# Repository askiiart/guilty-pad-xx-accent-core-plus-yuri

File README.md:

# Guilty Pad XX Λ Core Plus R

This is a pretty simple TKL keyboard with backlighting, an OLED, and a rotary encoder. The fancy trick is that it's designed to work with the [GUILTY PAD -GAY-](https://github.com/askiiart/guilty-pad-gay), so you can do whatever you want with it via Bluetooth. Connect them together and use the hackpad as macro key combos or something, literally anything!

---

The woke left made me add yuri (I actually haven't added any yet, busy doing actually useful stuff)

## Bill of Materials

| Name                                                                       | Link                                                                       | Unit price | Quantity needed | MOQ | Multiple | Total per item |
| -------------------------------------------------------------------------- | -------------------------------------------------------------------------- | ---------- | --------------- | --- | -------- | -------------- |
| XIAO nrf52840                                                              | <https://www.seeedstudio.com/Seeed-XIAO-BLE-nRF52840-p-5201.html>          | 8.99       | 1               | 1   | 1        | 8.99           |
| 0402 4.7k resistors (GR0402J4K7TAG00)                                      | <https://www.lcsc.com/product-detail/C49656853.html>                       | 0          | 2               | 100 | 100      | 0.04           |
| Rotary encoder w/ switch (EC11E18244A5)                                    | <https://www.lcsc.com/product-detail/C255515.html>                         | 2.05       | 1               | 1   | 1        | 2.05           |
| 0402 806k resistor (SCR0402F806K)                                          | <https://www.lcsc.com/product-detail/C3016043.html>                        | 0          | 1               | 100 | 100      | 0.05           |
| 0402 2M resistor (GR0402J2MTAG00)                                          | <https://www.lcsc.com/product-detail/C49653113.html>                       | 0          | 1               | 100 | 100      | 0.04           |
| 0603 10uF capacitor (CL10A106MQ8NNNC)                                      | <https://www.lcsc.com/product-detail/C1691.html>                           | 0          | 1               | 50  | 50       | 0.24           |
| 60x Mill-Max hotswap sockets                                               | <https://keeb.io/products/mill-max-hotswap-sockets?variant=32377167511646> | 7.99       | 3               | 1   | 1        | 23.97          |
| 20x SK6803MINI-E (LEDs)                                                    | <https://www.aliexpress.us/item/3256807898532204.html>                     | 31.16      | 5               | 1   | 1        | 24.7           |
| 22 AWG wires w/ JST XH connectors                                          | <https://www.aliexpress.us/item/3256803495901819.html>                     | 0.99       | 1               | 1   | 1        | 0.99           |
| Complimentary P/N channel MOSFETs (G1NP02ELL)                              | <https://www.lcsc.com/product-detail/C840056.html>                         | 0.03       | 1               | 20  | 20       | 0.66           |
| 15 uH Inductor (SLW4030S150MST)                                            | <https://www.lcsc.com/product-detail/C206361.html>                         | 0.07       | 1               | 10  | 10       | 0.69           |
| 5V boost converter (H8118A40PR)                                            | <https://www.lcsc.com/product-detail/C410998.html>                         | 0.13       | 1               | 5   | 5        | 0.66           |
| Diodes (1N4001)                                                            | <https://www.lcsc.com/product-detail/C2909965.html>                        | 0          | 89              | 50  | 50       | 0.41           |
| Level shifter (74LV1T08GW-TP)                                              | <https://www.lcsc.com/product-detail/C42460230.html>                       | 0.06       | 1               | 10  | 10       | 0.57           |
| 90x MX switches (Holy Panda 55g)                                           | <https://www.aliexpress.us/item/3256805924985540.html>                     | 5.49       | 1               | 1   | 1        | 5.49           |
| IO expander (AW9523BTQR)                                                   | <https://www.lcsc.com/product-detail/C148077.html>                         | 0.35       | 1               | 1   | 1        | 0.35           |
| Keycaps                                                                    | <https://www.aliexpress.us/item/3256809006592332.html>                     | 0.99       | 1               | 1   | 1        | 0.99           |
| 5000mAh 307090 lipo                                                        | <https://www.aliexpress.us/item/3256809787664995.html>                     | $5.18      | 1               | 1   | 1        | 4.18           |
| M2 screws and heat-set inserts (10x M2x3 inserts, 6x M2x4 (5?), 4x M2xTBD) | <https://www.aliexpress.us/item/3256807644176828.html>                     | 0.99       | 1               | 1   | 0.99     | 0.99           |
| 0.91" 128x32 OLED                                                          | <https://www.aliexpress.us/item/3256804386173217.html>                     | 0.99       | 1               | 1   | 0.99     | 0.99           |
|                                                                            |                                                                            |            |                 |     |          |                |
| Component Total                                                            |                                                                            |            |                 |     |          | 78.05          |
|                                                                            |                                                                            |            |                 |     |          |                |
| PCB total                                                                  |                                                                            |            |                 |     |          | 29.74          |
| Seeed studio shipping                                                      |                                                                            |            |                 |     |          | 5.46           |
| keeb.io shipping                                                           |                                                                            |            |                 |     |          | 6.37           |
| SK6803MINI-E shipping                                                      |                                                                            |            |                 |     |          | 6.52           |
| 5000mAh lipo shipping                                                      |                                                                            |            |                 |     |          | 5.41           |
| LCSC shipping & handling                                                   |                                                                            |            |                 |     |          | 11.71          |
|                                                                            |                                                                            |            |                 |     |          |                |
| Subtotal                                                                   |                                                                            |            |                 |     |          | 143.25         |
| Without mill-max sockets                                                   |                                                                            |            |                 |     |          | 112.91         |
|                                                                            |                                                                            |            |                 |     |          |                |
| Total                                                                      |                                                                            |            |                 |     |          | 155.07         |
| **Without mill-max sockets**                                               |                                                                            |            |                 |     |          | 122.23         |

## TODO

- redo routing everything
- [crystal](https://www.lcsc.com/product-detail/C18213028.html)
  - [capacitors](https://www.lcsc.com/product-detail/C501818.html)
- [antenna](https://www.lcsc.com/product-detail/C42395593.html)
- [usb resistors](https://www.lcsc.com/product-detail/C2906874.html)
- battery management chip: [SGM40567](https://www.lcsc.com/product-detail/C5141336.html)
  - [digipot for PROG](https://www.lcsc.com/product-detail/C649485.html)
- [usb-c port](https://jlcpcb.com/partdetail/Korean_HropartsElec-TYPE_C_31_M12/C165948)
- reset button
  - [reset button?](https://www.aliexpress.us/item/3256806601702089.html)
  - [reset buttonnnnnn?](https://www.lcsc.com/product-detail/C49234121.html)
- [pmos for voltage regulators](https://www.lcsc.com/product-detail/C239037.html)
- [D4 (3A)](https://www.lcsc.com/product-detail/C97127.html)
- [D1, D2, D3, D7 (1A)](https://www.lcsc.com/product-detail/C2912031.html)
- [D5, D6 (2A)](https://www.lcsc.com/product-detail/C153761.html)
- [5V boost converter](https://www.lcsc.com/product-detail/C621881.html)

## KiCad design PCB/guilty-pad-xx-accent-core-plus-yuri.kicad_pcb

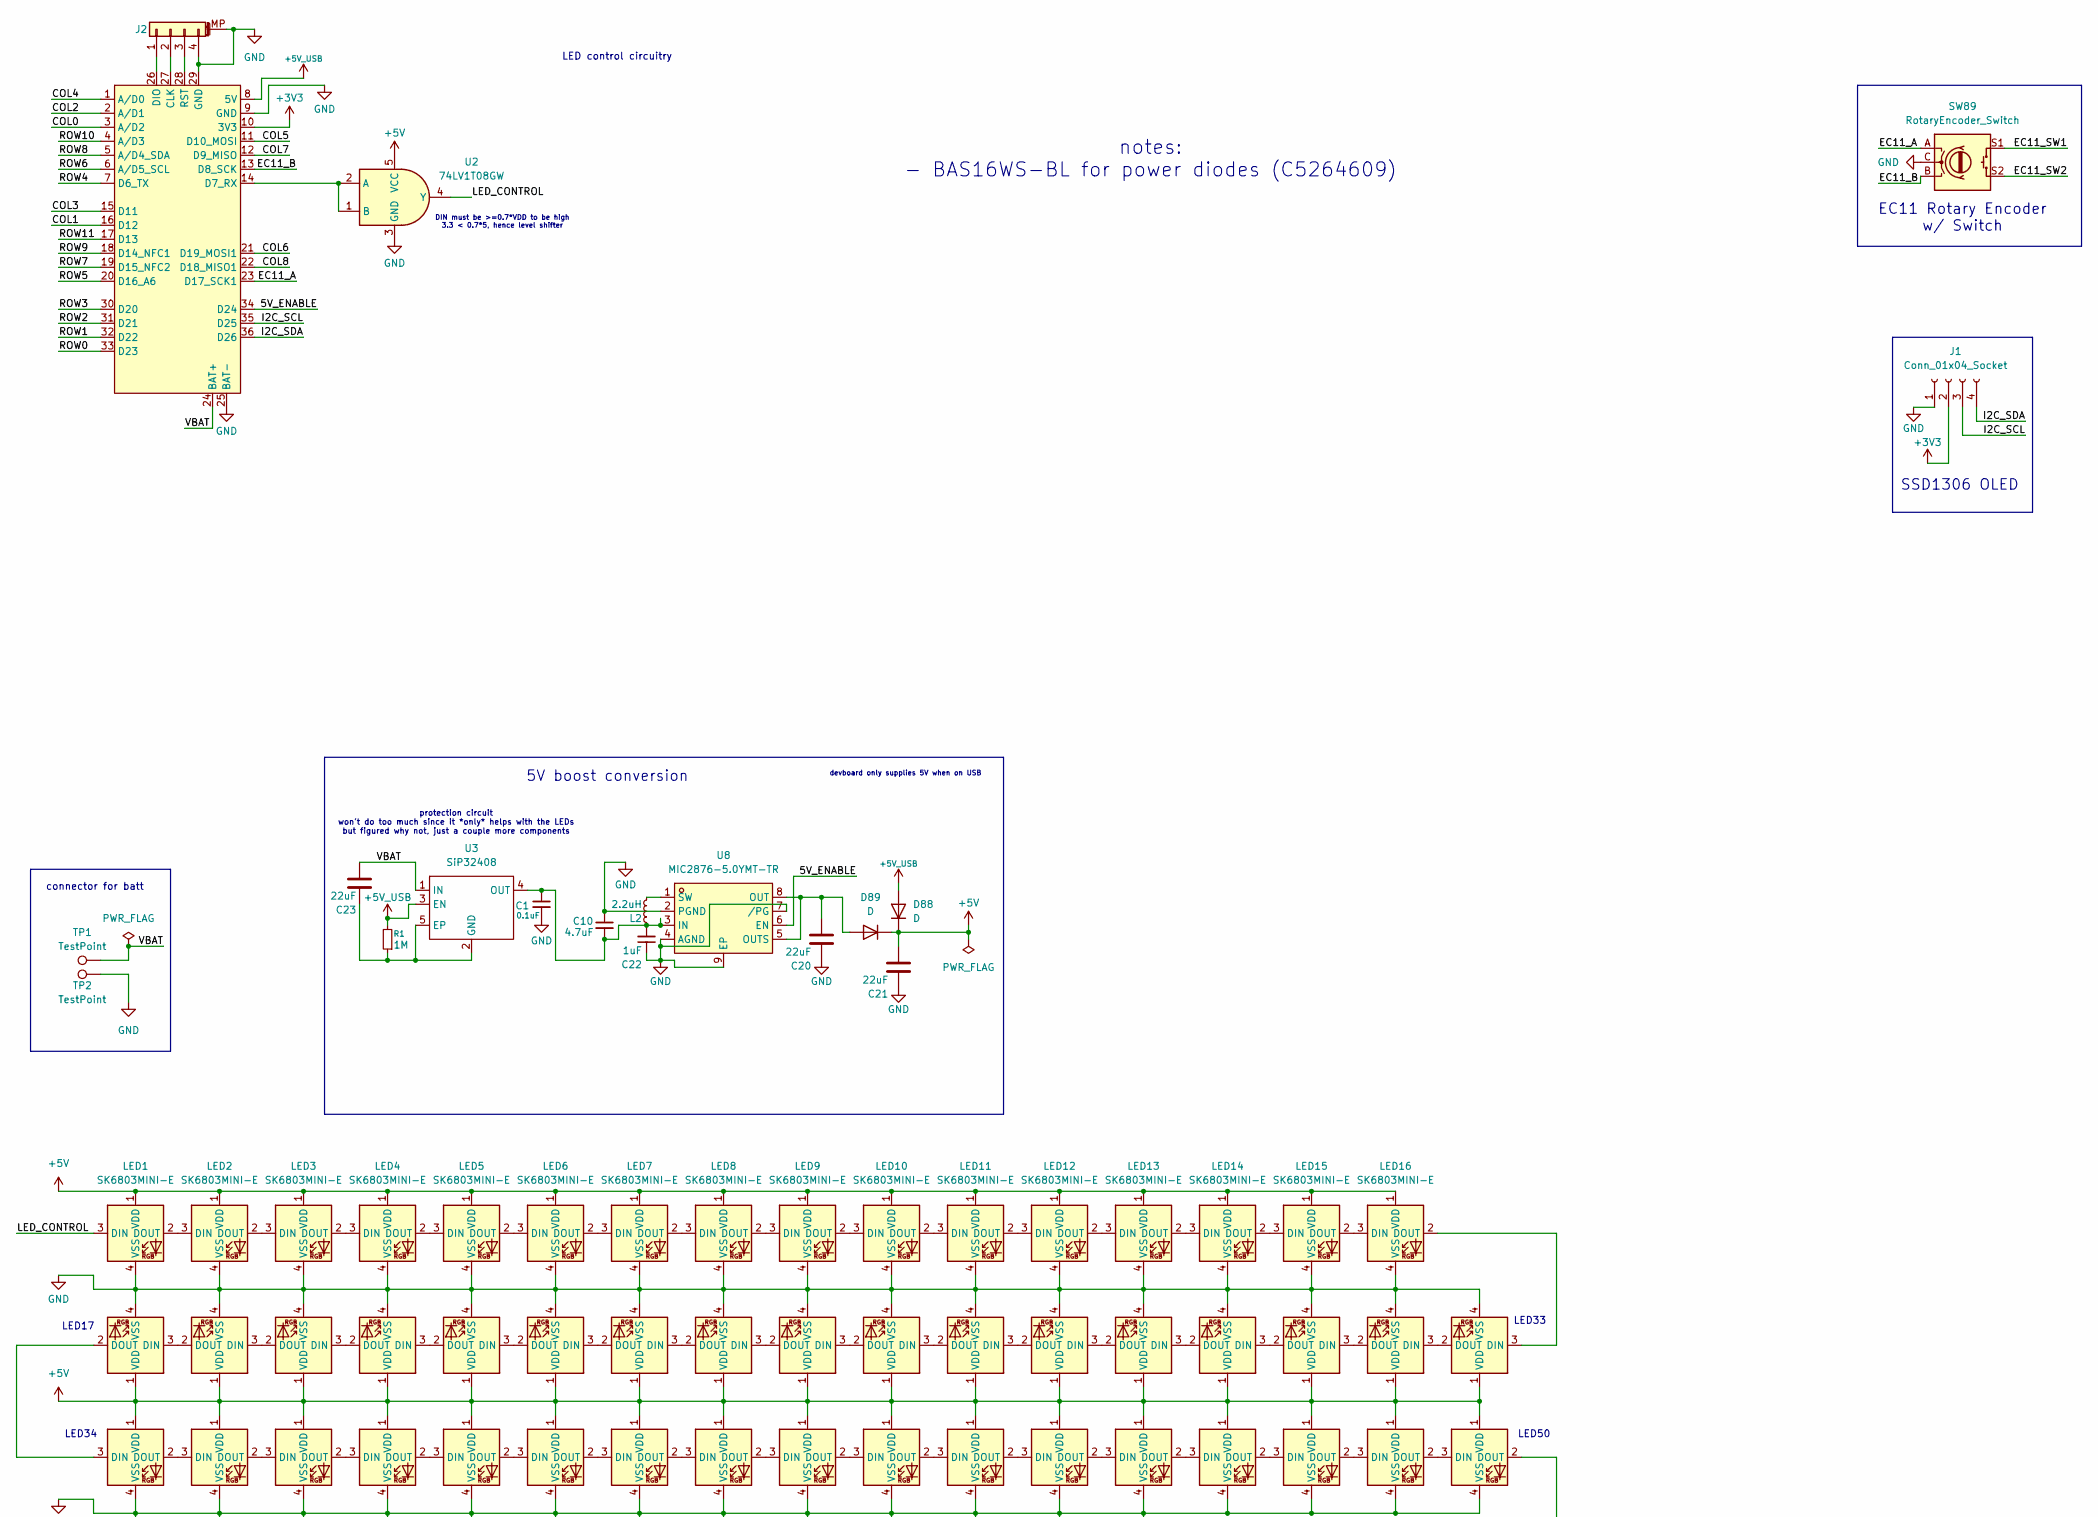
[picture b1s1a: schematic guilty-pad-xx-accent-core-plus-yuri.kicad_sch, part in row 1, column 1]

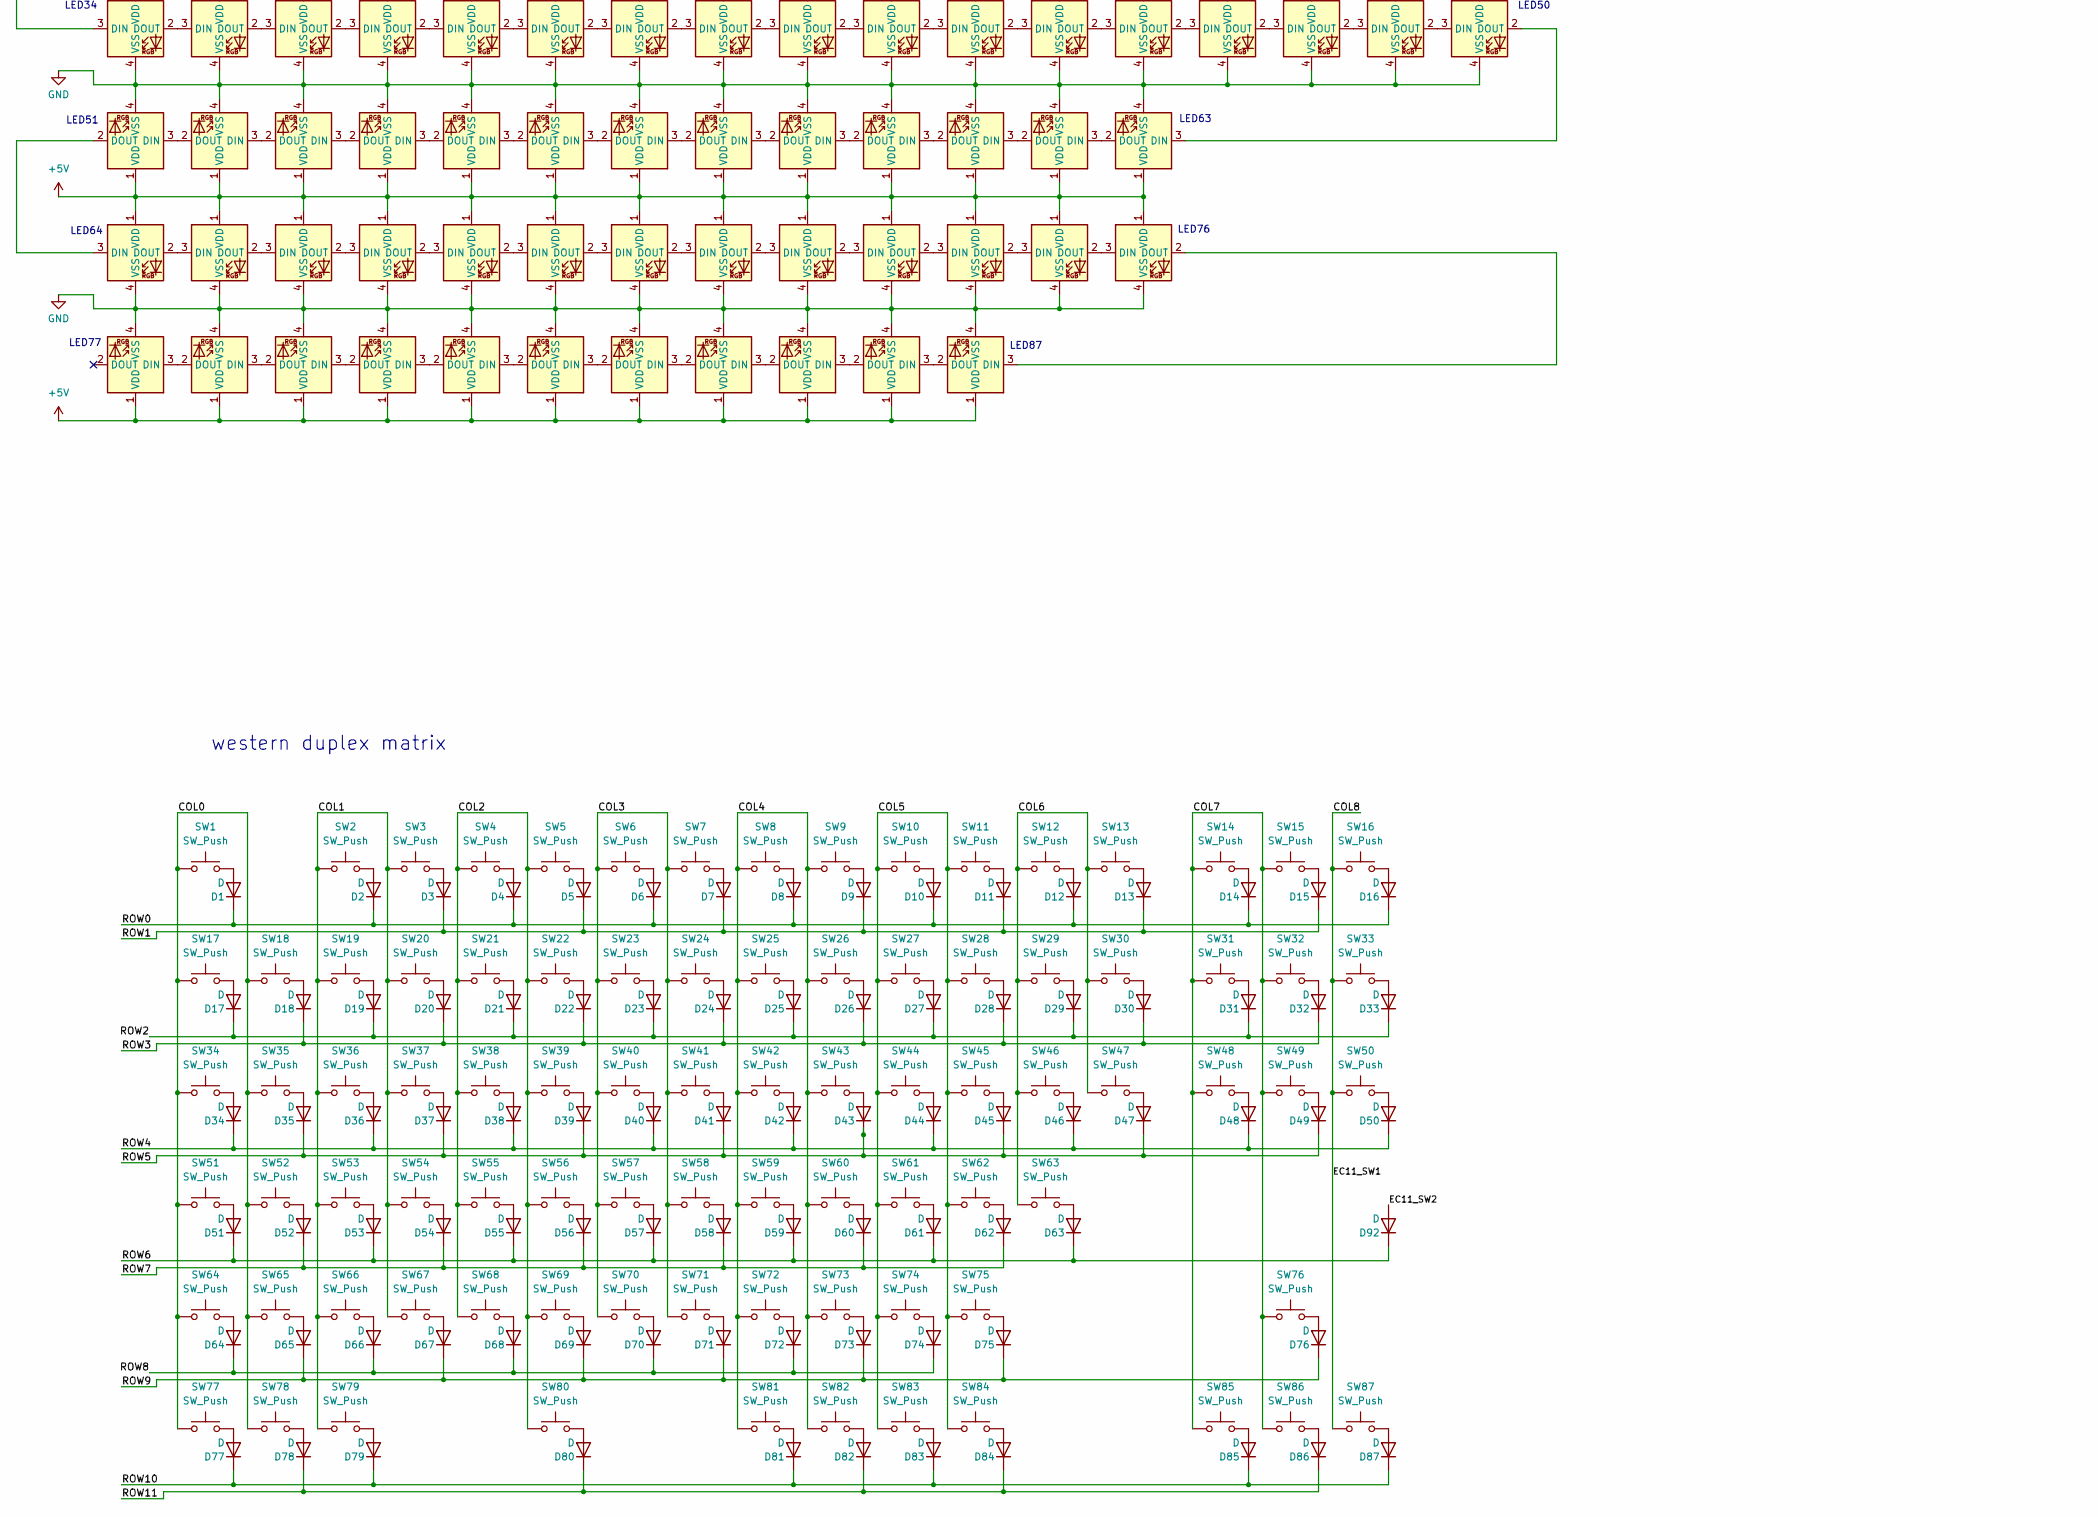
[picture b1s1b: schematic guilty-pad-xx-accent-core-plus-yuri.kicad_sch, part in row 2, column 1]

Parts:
C1: 0.1uF; C_0603_1608Metric
C10: 4.7uF; C_0603_1608Metric
C20, C21, C23: 22uF; C_0603_1608Metric
C22: 1uF; C_0603_1608Metric
D1, D2, D3, D4, D5, D6, D7, D8, D9, D10, D11, D12, D13, D14, D15, D16, D17, D18, D19, D20, D21, D22, D23, D24, D25, D26, D27, D28, D29, D30, D31, D32, D33, D34, D35, D36, D37, D38, D39, D40, D41, D42, D43, D44, D45, D46, D47, D48, D49, D50, D51, D52, D53, D54, D55, D56, D57, D58, D59, D60, D61, D62, D63, D64, D65, D66, D67, D68, D69, D70, D71, D72, D73, D74, D75, D76, D77, D78, D79, D80, D81, D82, D83, D84, D85, D86, D87, D88, D89, D92: D; D_SOD-323_HandSoldering
J1: Conn_01x04_Socket; SSD1306-0.91-OLED-4pin-128x32
J2: Conn_01x04_MountingPin; JST_SH_BM04B-SRSS-TB_1x04-1MP_P1.00mm_Vertical
L2: 2.2uH; L_0805_2012Metric
LED1, LED2, LED3, LED4, LED5, LED6, LED7, LED8, LED9, LED10, LED11, LED12, LED13, LED14, LED15, LED16, LED17, LED18, LED19, LED20, LED21, LED22, LED23, LED24, LED25, LED26, LED27, LED28, LED29, LED30, LED31, LED32, LED33, LED34, LED35, LED36, LED37, LED38, LED39, LED40, LED41, LED42, LED43, LED44, LED45, LED46, LED47, LED48, LED49, LED50, LED51, LED52, LED53, LED54, LED55, LED56, LED57, LED58, LED59, LED60, LED61, LED62, LED63, LED64, LED65, LED66, LED67, LED68, LED69, LED70, LED71, LED72, LED73, LED74, LED75, LED76, LED77, LED78, LED79, LED80, LED81, LED82, LED83, LED84, LED85, LED86, LED87: SK6803MINI-E; LED_6028R
R1: 1M; R_0603_1608Metric
SW1, SW2, SW3, SW4, SW5, SW6, SW7, SW8, SW9, SW10, SW11, SW12, SW13, SW14, SW15, SW16, SW17, SW18, SW19, SW20, SW21, SW22, SW23, SW24, SW25, SW26, SW27, SW28, SW29, SW30, SW31, SW32, SW33, SW35, SW36, SW37, SW38, SW39, SW40, SW41, SW42, SW43, SW44, SW45, SW46, SW48, SW49, SW50, SW52, SW53, SW54, SW55, SW56, SW57, SW58, SW59, SW60, SW61, SW62, SW63, SW64, SW65, SW66, SW67, SW68, SW69, SW70, SW71, SW72, SW73, SW74, SW75, SW76, SW80, SW85, SW86, SW87: SW_Push; SW_MX_HS_CPG151101S11_1u
SW34, SW47: SW_Push; SW_MX_HS_CPG151101S11_1.5u
SW51: SW_Push; SW_MX_HS_CPG151101S11_1.75u
SW77, SW78, SW79, SW81, SW82, SW83, SW84: SW_Push; SW_MX_HS_CPG151101S11_1.25u
SW89: RotaryEncoder_Switch; RotaryEncoder_Alps_EC11E-Switch_Vertical_H20mm
TP1, TP2: TestPoint; TestPoint_Pad_2.0x2.0mm
U1: Guilty Devboard Xrd; Guilty Devboard Xrd - SMD
U2: 74LV1T08GW; SOT-353_SC-70-5
U3: SiP32408; UDFN-4-1EP_1.2x1.6mm_P0.5mm_EP0.86x0.5mm
U8: MIC2876-5.0YMT-TR; UDFN-8_L2.0-W2.0-P0.50-BL-EP; LCSC Part C621881

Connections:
+3V3: J1.2, U1.10 (3V3)
+5V: C21.2, D88.1 (K), D89.1 (K), LED1.1 (VDD), LED2.1 (VDD), LED3.1 (VDD), LED4.1 (VDD), LED5.1 (VDD), LED6.1 (VDD), LED7.1 (VDD), LED8.1 (VDD), LED9.1 (VDD), LED10.1 (VDD), LED11.1 (VDD), LED12.1 (VDD), LED13.1 (VDD), LED14.1 (VDD), LED15.1 (VDD), LED16.1 (VDD), LED17.1 (VDD), LED18.1 (VDD), LED19.1 (VDD), LED20.1 (VDD), LED21.1 (VDD), LED22.1 (VDD), LED23.1 (VDD), LED24.1 (VDD), LED25.1 (VDD), LED26.1 (VDD), LED27.1 (VDD), LED28.1 (VDD), LED29.1 (VDD), LED30.1 (VDD), LED31.1 (VDD), LED32.1 (VDD), LED33.1 (VDD), LED34.1 (VDD), LED35.1 (VDD), LED36.1 (VDD), LED37.1 (VDD), LED38.1 (VDD), LED39.1 (VDD), LED40.1 (VDD), LED41.1 (VDD), LED42.1 (VDD), LED43.1 (VDD), LED44.1 (VDD), LED45.1 (VDD), LED46.1 (VDD), LED47.1 (VDD), LED48.1 (VDD), LED49.1 (VDD), LED50.1 (VDD), LED51.1 (VDD), LED52.1 (VDD), LED53.1 (VDD), LED54.1 (VDD), LED55.1 (VDD), LED56.1 (VDD), LED57.1 (VDD), LED58.1 (VDD), LED59.1 (VDD), LED60.1 (VDD), LED61.1 (VDD), LED62.1 (VDD), LED63.1 (VDD), LED64.1 (VDD), LED65.1 (VDD), LED66.1 (VDD), LED67.1 (VDD), LED68.1 (VDD), LED69.1 (VDD), LED70.1 (VDD), LED71.1 (VDD), LED72.1 (VDD), LED73.1 (VDD), LED74.1 (VDD), LED75.1 (VDD), LED76.1 (VDD), LED77.1 (VDD), LED78.1 (VDD), LED79.1 (VDD), LED80.1 (VDD), LED81.1 (VDD), LED82.1 (VDD), LED83.1 (VDD), LED84.1 (VDD), LED85.1 (VDD), LED86.1 (VDD), LED87.1 (VDD), U2.5 (VCC)
+5V_USB: D88.2 (A), R1.2, U1.8 (5V), U3.3 (EN)
/5V_ENABLE: U1.34 (D24), U8.6 (EN)
/COL0: SW1.1, SW17.1, SW18.1, SW34.1, SW35.1, SW51.1, SW52.1, SW64.1, SW65.1, SW77.1, SW78.1, U1.3 (A/D2)
/COL1: SW2.1, SW3.1, SW19.1, SW20.1, SW36.1, SW37.1, SW53.1, SW54.1, SW66.1, SW67.1, SW79.1, U1.16 (D12)
/COL2: SW4.1, SW5.1, SW21.1, SW22.1, SW38.1, SW39.1, SW55.1, SW56.1, SW68.1, SW69.1, SW80.1, U1.2 (A/D1)
/COL3: SW6.1, SW7.1, SW23.1, SW24.1, SW40.1, SW41.1, SW57.1, SW58.1, SW70.1, SW71.1, U1.15 (D11)
/COL4: SW8.1, SW9.1, SW25.1, SW26.1, SW42.1, SW43.1, SW59.1, SW60.1, SW72.1, SW73.1, SW81.1, SW82.1, U1.1 (A/D0)
/COL5: SW10.1, SW11.1, SW27.1, SW28.1, SW44.1, SW45.1, SW61.1, SW62.1, SW74.1, SW75.1, SW83.1, SW84.1, U1.11 (D10_MOSI)
/COL6: SW12.1, SW13.1, SW29.1, SW30.1, SW46.1, SW47.1, SW63.1, U1.21 (D19_MOSI1)
/COL7: SW14.1, SW15.1, SW31.1, SW32.1, SW48.1, SW49.1, SW76.1, SW85.1, SW86.1, U1.12 (D9_MISO)
/COL8: SW16.1, SW33.1, SW50.1, SW87.1, SW89.S1, U1.22 (D18_MISO1)
/EC11_A: SW89.A, U1.23 (D17_SCK1)
/EC11_B: SW89.B, U1.13 (D8_SCK)
/EC11_SW2: D92.2 (A), SW89.S2
/I2C_SCL: J1.3, U1.35 (D25)
/I2C_SDA: J1.4, U1.36 (D26)
/LED_CONTROL: LED1.3 (DIN), U2.4 (Y)
/ROW0: D1.1 (K), D2.1 (K), D4.1 (K), D6.1 (K), D8.1 (K), D10.1 (K), D12.1 (K), D14.1 (K), D16.1 (K), U1.33 (D23)
/ROW1: D3.1 (K), D5.1 (K), D7.1 (K), D9.1 (K), D11.1 (K), D13.1 (K), D15.1 (K), U1.32 (D22)
/ROW2: D17.1 (K), D19.1 (K), D21.1 (K), D23.1 (K), D25.1 (K), D27.1 (K), D29.1 (K), D31.1 (K), D33.1 (K), U1.31 (D21)
/ROW3: D18.1 (K), D20.1 (K), D22.1 (K), D24.1 (K), D26.1 (K), D28.1 (K), D30.1 (K), D32.1 (K), U1.30 (D20)
/ROW4: D34.1 (K), D36.1 (K), D38.1 (K), D40.1 (K), D42.1 (K), D44.1 (K), D46.1 (K), D48.1 (K), D50.1 (K), U1.7 (D6_TX)
/ROW5: D35.1 (K), D37.1 (K), D39.1 (K), D41.1 (K), D43.1 (K), D45.1 (K), D47.1 (K), D49.1 (K), U1.20 (D16_A6)
/ROW6: D51.1 (K), D53.1 (K), D55.1 (K), D57.1 (K), D59.1 (K), D61.1 (K), D63.1 (K), D92.1 (K), U1.6 (A/D5_SCL)
/ROW7: D52.1 (K), D54.1 (K), D56.1 (K), D58.1 (K), D60.1 (K), D62.1 (K), U1.19 (D15_NFC2)
/ROW8: D64.1 (K), D66.1 (K), D68.1 (K), D70.1 (K), D72.1 (K), D74.1 (K), U1.5 (A/D4_SDA)
/ROW9: D65.1 (K), D67.1 (K), D69.1 (K), D71.1 (K), D73.1 (K), D75.1 (K), D76.1 (K), U1.18 (D14_NFC1)
/ROW10: D77.1 (K), D79.1 (K), D81.1 (K), D83.1 (K), D85.1 (K), D87.1 (K), U1.4 (A/D3)
/ROW11: D78.1 (K), D80.1 (K), D82.1 (K), D84.1 (K), D86.1 (K), U1.17 (D13)
/VBAT: C23.2, TP1.1 (1_1), U1.24 (BAT+), U3.1 (IN)
unnamed: D1.2 (A), SW1.2
unnamed: D2.2 (A), SW2.2
unnamed: D3.2 (A), SW3.2
unnamed: D4.2 (A), SW4.2
unnamed: D5.2 (A), SW5.2
unnamed: D6.2 (A), SW6.2
unnamed: D7.2 (A), SW7.2
unnamed: D8.2 (A), SW8.2
unnamed: D9.2 (A), SW9.2
unnamed: D10.2 (A), SW10.2
unnamed: D11.2 (A), SW11.2
unnamed: D12.2 (A), SW12.2
unnamed: D13.2 (A), SW13.2
unnamed: D14.2 (A), SW14.2
unnamed: D15.2 (A), SW15.2
unnamed: D16.2 (A), SW16.2
unnamed: D17.2 (A), SW17.2
unnamed: D18.2 (A), SW18.2
unnamed: D19.2 (A), SW19.2
unnamed: D20.2 (A), SW20.2
unnamed: D21.2 (A), SW21.2
unnamed: D22.2 (A), SW22.2
unnamed: D23.2 (A), SW23.2
unnamed: D24.2 (A), SW24.2
unnamed: D25.2 (A), SW25.2
unnamed: D26.2 (A), SW26.2
unnamed: D27.2 (A), SW27.2
unnamed: D28.2 (A), SW28.2
unnamed: D29.2 (A), SW29.2
unnamed: D30.2 (A), SW30.2
unnamed: D31.2 (A), SW31.2
unnamed: D32.2 (A), SW32.2
unnamed: D33.2 (A), SW33.2
unnamed: D34.2 (A), SW34.2
unnamed: D35.2 (A), SW35.2
unnamed: D36.2 (A), SW36.2
unnamed: D37.2 (A), SW37.2
unnamed: D38.2 (A), SW38.2
unnamed: D39.2 (A), SW39.2
unnamed: D40.2 (A), SW40.2
unnamed: D41.2 (A), SW41.2
unnamed: D42.2 (A), SW42.2
unnamed: D43.2 (A), SW43.2
unnamed: D44.2 (A), SW44.2
unnamed: D45.2 (A), SW45.2
unnamed: D46.2 (A), SW46.2
unnamed: D47.2 (A), SW47.2
unnamed: D48.2 (A), SW48.2
unnamed: D49.2 (A), SW49.2
unnamed: D50.2 (A), SW50.2
unnamed: D51.2 (A), SW51.2
unnamed: D52.2 (A), SW52.2
unnamed: D53.2 (A), SW53.2
unnamed: D54.2 (A), SW54.2
unnamed: D55.2 (A), SW55.2
unnamed: D56.2 (A), SW56.2
unnamed: D57.2 (A), SW57.2
unnamed: D58.2 (A), SW58.2
unnamed: D59.2 (A), SW59.2
unnamed: D60.2 (A), SW60.2
unnamed: D61.2 (A), SW61.2
unnamed: D62.2 (A), SW62.2
unnamed: D63.2 (A), SW63.2
unnamed: D64.2 (A), SW64.2
unnamed: D65.2 (A), SW65.2
unnamed: D66.2 (A), SW66.2
unnamed: D67.2 (A), SW67.2
unnamed: D68.2 (A), SW68.2
unnamed: D69.2 (A), SW69.2
unnamed: D70.2 (A), SW70.2
unnamed: D71.2 (A), SW71.2
unnamed: D72.2 (A), SW72.2
unnamed: D73.2 (A), SW73.2
unnamed: D74.2 (A), SW74.2
unnamed: D75.2 (A), SW75.2
unnamed: D76.2 (A), SW76.2
unnamed: D77.2 (A), SW77.2
unnamed: D78.2 (A), SW78.2
unnamed: D79.2 (A), SW79.2
unnamed: D80.2 (A), SW80.2
unnamed: D81.2 (A), SW81.2
unnamed: D82.2 (A), SW82.2
unnamed: D83.2 (A), SW83.2
unnamed: D84.2 (A), SW84.2
unnamed: D85.2 (A), SW85.2
unnamed: D86.2 (A), SW86.2
unnamed: D87.2 (A), SW87.2
unnamed: C20.2, D89.2 (A), U8.5 (OUTS), U8.8 (OUT)
unnamed: J2.1, U1.26 (DIO)
unnamed: J2.2, U1.27 (CLK)
unnamed: J2.3, U1.28 (RST)
unnamed: LED1.2 (DOUT), LED2.3 (DIN)
unnamed: LED2.2 (DOUT), LED3.3 (DIN)
unnamed: LED3.2 (DOUT), LED4.3 (DIN)
unnamed: LED4.2 (DOUT), LED5.3 (DIN)
unnamed: LED5.2 (DOUT), LED6.3 (DIN)
unnamed: LED6.2 (DOUT), LED7.3 (DIN)
unnamed: LED7.2 (DOUT), LED8.3 (DIN)
unnamed: LED8.2 (DOUT), LED9.3 (DIN)
unnamed: LED9.2 (DOUT), LED10.3 (DIN)
unnamed: LED10.2 (DOUT), LED11.3 (DIN)
unnamed: LED11.2 (DOUT), LED12.3 (DIN)
unnamed: LED12.2 (DOUT), LED13.3 (DIN)
unnamed: LED13.2 (DOUT), LED14.3 (DIN)
unnamed: LED14.2 (DOUT), LED15.3 (DIN)
unnamed: LED15.2 (DOUT), LED16.3 (DIN)
unnamed: LED16.2 (DOUT), LED33.3 (DIN)
unnamed: LED17.3 (DIN), LED18.2 (DOUT)
unnamed: LED17.2 (DOUT), LED34.3 (DIN)
unnamed: LED18.3 (DIN), LED19.2 (DOUT)
unnamed: LED19.3 (DIN), LED20.2 (DOUT)
unnamed: LED20.3 (DIN), LED21.2 (DOUT)
unnamed: LED21.3 (DIN), LED22.2 (DOUT)
unnamed: LED22.3 (DIN), LED23.2 (DOUT)
unnamed: LED23.3 (DIN), LED24.2 (DOUT)
unnamed: LED24.3 (DIN), LED25.2 (DOUT)
unnamed: LED25.3 (DIN), LED26.2 (DOUT)
unnamed: LED26.3 (DIN), LED27.2 (DOUT)
unnamed: LED27.3 (DIN), LED28.2 (DOUT)
unnamed: LED28.3 (DIN), LED29.2 (DOUT)
unnamed: LED29.3 (DIN), LED30.2 (DOUT)
unnamed: LED30.3 (DIN), LED31.2 (DOUT)
unnamed: LED31.3 (DIN), LED32.2 (DOUT)
unnamed: LED32.3 (DIN), LED33.2 (DOUT)
unnamed: LED34.2 (DOUT), LED35.3 (DIN)
unnamed: LED35.2 (DOUT), LED36.3 (DIN)
unnamed: LED36.2 (DOUT), LED37.3 (DIN)
unnamed: LED37.2 (DOUT), LED38.3 (DIN)
unnamed: LED38.2 (DOUT), LED39.3 (DIN)
unnamed: LED39.2 (DOUT), LED40.3 (DIN)
unnamed: LED40.2 (DOUT), LED41.3 (DIN)
unnamed: LED41.2 (DOUT), LED42.3 (DIN)
unnamed: LED42.2 (DOUT), LED43.3 (DIN)
unnamed: LED43.2 (DOUT), LED44.3 (DIN)
unnamed: LED44.2 (DOUT), LED45.3 (DIN)
unnamed: LED45.2 (DOUT), LED46.3 (DIN)
unnamed: LED46.2 (DOUT), LED47.3 (DIN)
unnamed: LED47.2 (DOUT), LED48.3 (DIN)
unnamed: LED48.2 (DOUT), LED49.3 (DIN)
unnamed: LED49.2 (DOUT), LED50.3 (DIN)
unnamed: LED50.2 (DOUT), LED63.3 (DIN)
unnamed: LED51.3 (DIN), LED52.2 (DOUT)
unnamed: LED51.2 (DOUT), LED64.3 (DIN)
unnamed: LED52.3 (DIN), LED53.2 (DOUT)
unnamed: LED53.3 (DIN), LED54.2 (DOUT)
unnamed: LED54.3 (DIN), LED55.2 (DOUT)
unnamed: LED55.3 (DIN), LED56.2 (DOUT)
unnamed: LED56.3 (DIN), LED57.2 (DOUT)
unnamed: LED57.3 (DIN), LED58.2 (DOUT)
unnamed: LED58.3 (DIN), LED59.2 (DOUT)
unnamed: LED59.3 (DIN), LED60.2 (DOUT)
unnamed: LED60.3 (DIN), LED61.2 (DOUT)
unnamed: LED61.3 (DIN), LED62.2 (DOUT)
unnamed: LED62.3 (DIN), LED63.2 (DOUT)
unnamed: LED64.2 (DOUT), LED65.3 (DIN)
unnamed: LED65.2 (DOUT), LED66.3 (DIN)
unnamed: LED66.2 (DOUT), LED67.3 (DIN)
unnamed: LED67.2 (DOUT), LED68.3 (DIN)
unnamed: LED68.2 (DOUT), LED69.3 (DIN)
unnamed: LED69.2 (DOUT), LED70.3 (DIN)
unnamed: LED70.2 (DOUT), LED71.3 (DIN)
unnamed: LED71.2 (DOUT), LED72.3 (DIN)
unnamed: LED72.2 (DOUT), LED73.3 (DIN)
unnamed: LED73.2 (DOUT), LED74.3 (DIN)
unnamed: LED74.2 (DOUT), LED75.3 (DIN)
unnamed: LED75.2 (DOUT), LED76.3 (DIN)
unnamed: LED76.2 (DOUT), LED87.3 (DIN)
unnamed: LED77.3 (DIN), LED78.2 (DOUT)
unnamed: LED78.3 (DIN), LED79.2 (DOUT)
unnamed: LED79.3 (DIN), LED80.2 (DOUT)
unnamed: LED80.3 (DIN), LED81.2 (DOUT)
unnamed: LED81.3 (DIN), LED82.2 (DOUT)
unnamed: LED82.3 (DIN), LED83.2 (DOUT)
unnamed: LED83.3 (DIN), LED84.2 (DOUT)
unnamed: LED84.3 (DIN), LED85.2 (DOUT)
unnamed: LED85.3 (DIN), LED86.2 (DOUT)
unnamed: LED86.3 (DIN), LED87.2 (DOUT)
unnamed: U1.14 (D7_RX), U2.1 (B), U2.2 (A)
unnamed: C1.1, C10.2, C22.2, L2.1, U3.4 (OUT), U8.3 (IN)
unnamed: L2.2, U8.1 (SW)

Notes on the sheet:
LED63
connector for batt
LED control circuitry
western duplex matrix
LED50
EC11 Rotary Encoder w/ Switch
notes: - BAS16WS-BL for power diodes (C5264609)
LED34
devboard only supplies 5V when on USB
LED17
LED51
protection circuit won't do too much since it *only* helps with the LEDs but figured why not, just a couple more components
LED87
LED76
DIN must be >=0.7*VDD to be high 3.3 < 0.7*5, hence level shifter
LED77
LED33
5V boost conversion
SSD1306 OLED
LED64

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
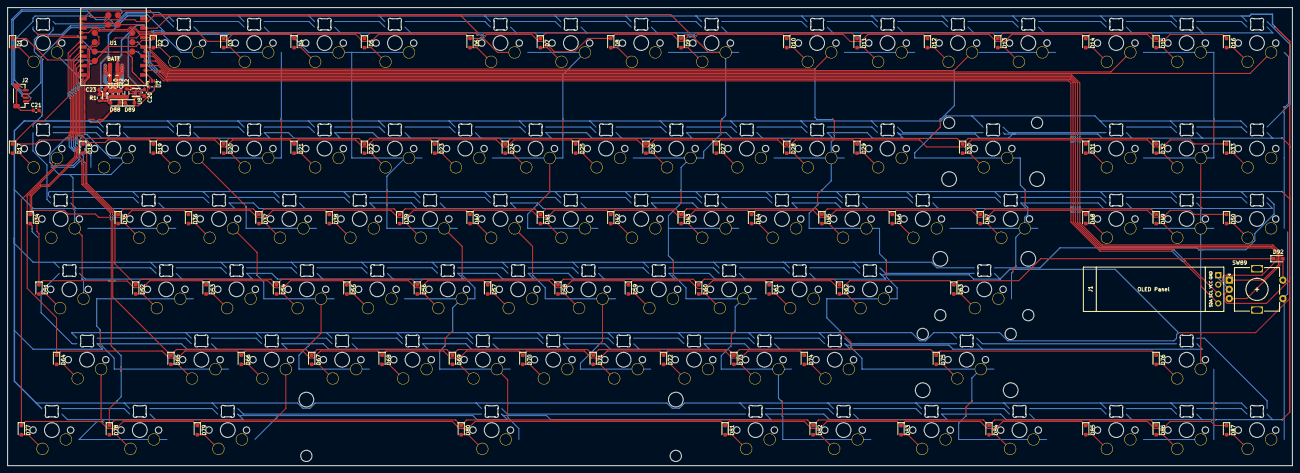
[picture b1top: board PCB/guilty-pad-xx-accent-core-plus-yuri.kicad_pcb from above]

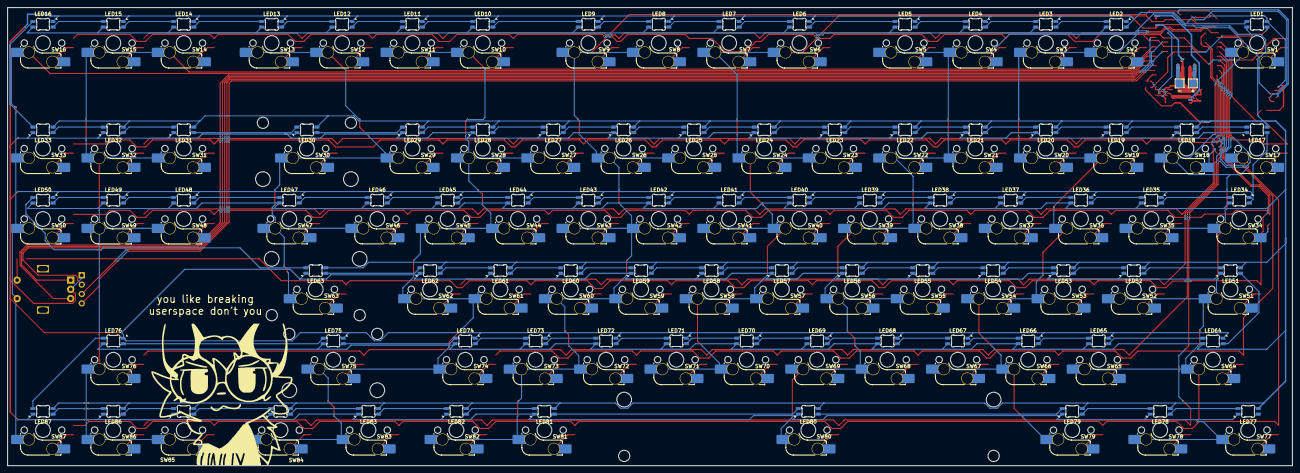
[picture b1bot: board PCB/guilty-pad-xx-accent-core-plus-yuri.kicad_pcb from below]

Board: 2 copper layers, 347.8 x 124.0 mm, 281 parts (176 on the bottom side), 213 nets.
